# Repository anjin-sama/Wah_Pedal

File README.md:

Inductorless Wah guitar pedal effect

https://gearip.net/inductorless-wah-guitar-pedal-effect/

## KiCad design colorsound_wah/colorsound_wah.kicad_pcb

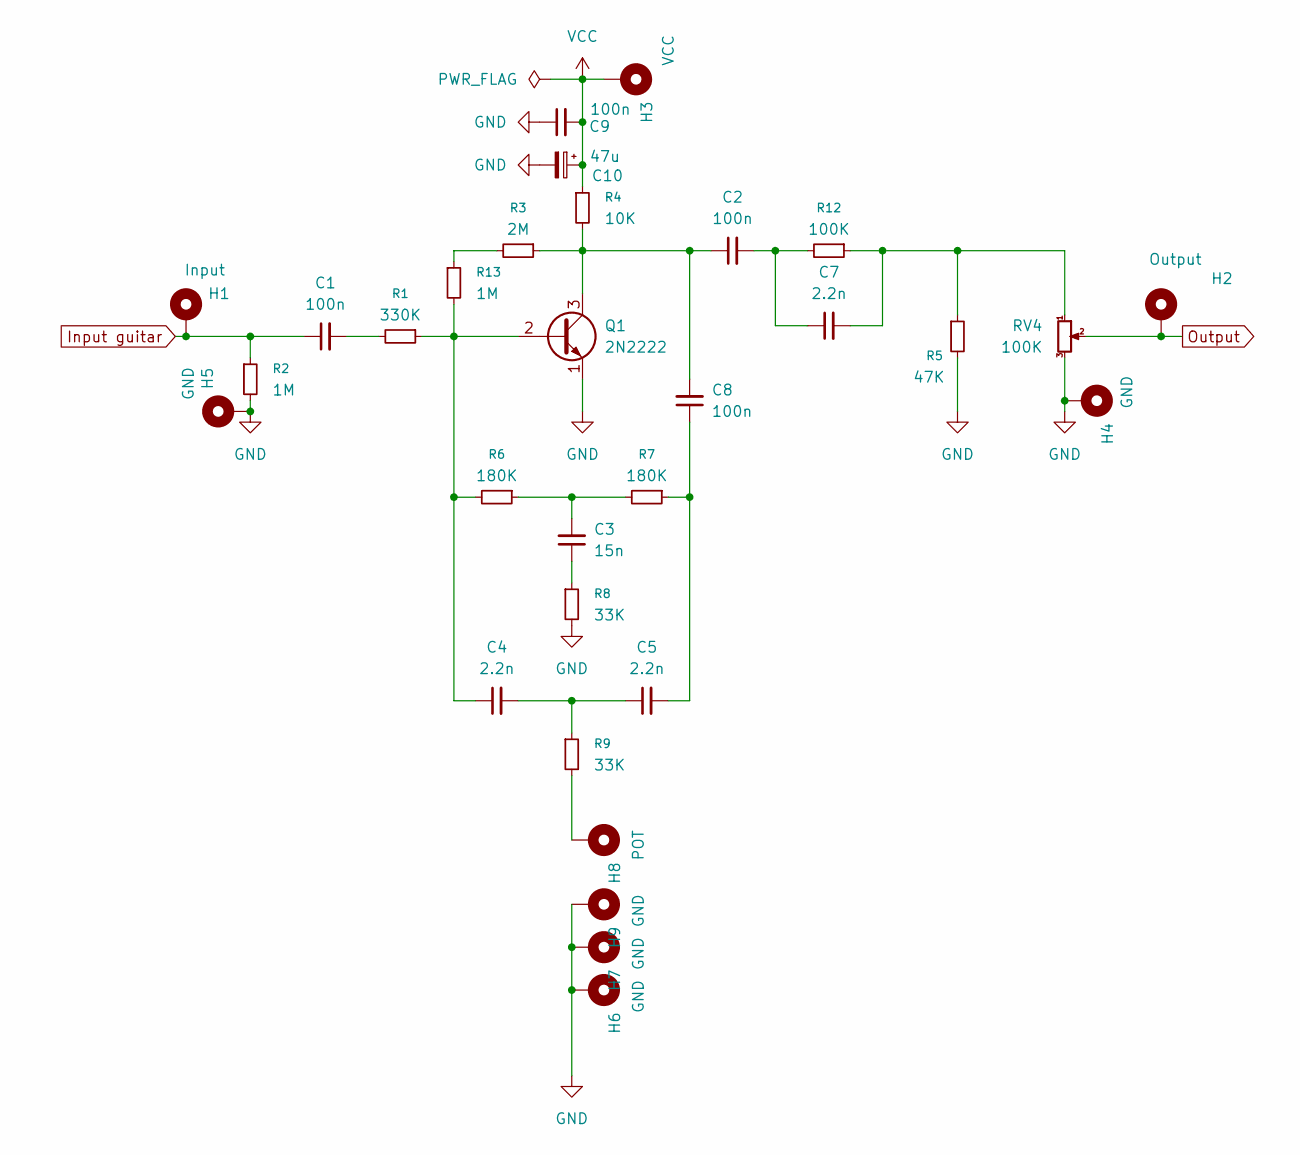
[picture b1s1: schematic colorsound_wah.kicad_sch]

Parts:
C1, C2, C8: 100n; C_Rect_L7.0mm_W2.0mm_P5.00mm
C3: 15n; C_Rect_L7.0mm_W2.0mm_P5.00mm
C4, C5, C7: 2.2n; C_Rect_L7.0mm_W2.0mm_P5.00mm
C9: 100n; C_Disc_D11.0mm_W5.0mm_P5.00mm
C10: 47u; CP_Radial_D5.0mm_P2.00mm
H1: Input; TestPoint_Loop_D2.50mm_Drill1.0mm_LowProfile
H2: Output; TestPoint_Loop_D2.50mm_Drill1.0mm_LowProfile
H3: VCC; TestPoint_Loop_D2.50mm_Drill1.0mm_LowProfile
H4, H5, H6, H7, H9: GND; TestPoint_Loop_D2.50mm_Drill1.85mm
H8: POT; TestPoint_Loop_D2.50mm_Drill1.0mm_LowProfile
Q1: 2N2222; TO-92L_Inline_Wide
R1: 330K; R_Axial_DIN0207_L6.3mm_D2.5mm_P10.16mm_Horizontal
R2, R13: 1M; R_Axial_DIN0207_L6.3mm_D2.5mm_P10.16mm_Horizontal
R3: 2M; R_Axial_DIN0207_L6.3mm_D2.5mm_P10.16mm_Horizontal
R4: 10K; R_Axial_DIN0207_L6.3mm_D2.5mm_P10.16mm_Horizontal
R5: 47K; R_Axial_DIN0207_L6.3mm_D2.5mm_P10.16mm_Horizontal
R6, R7: 180K; R_Axial_DIN0207_L6.3mm_D2.5mm_P10.16mm_Horizontal
R8, R9: 33K; R_Axial_DIN0207_L6.3mm_D2.5mm_P10.16mm_Horizontal
R12: 100K; R_Axial_DIN0207_L6.3mm_D2.5mm_P10.16mm_Horizontal
RV4: 100K; Potentiometer_ACP_CA9-H5_Horizontal

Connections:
GND: C9.1, C10.2, H4.1, H5.1, H6.1, H7.1, H9.1, Q1.1 (E), R2.2, R5.2, R8.2, RV4.3
Input guitar: C1.1, H1.1, R2.1
unnamed: C1.2, R1.2
unnamed: C2.2, C7.1, R12.2
unnamed: C3.1, R8.1
unnamed: C3.2, R6.1, R7.2
unnamed: C4.2, C5.1, R9.1
unnamed: C5.2, C8.1, R7.1
unnamed: C7.2, R5.1, R12.1, RV4.1
unnamed: H8.1, R9.2
unnamed: C4.1, Q1.2 (B), R1.1, R6.2, R13.2
unnamed: C2.1, C8.2, Q1.3 (C), R3.1, R4.2
unnamed: R3.2, R13.1
Output: H2.1, RV4.2
VCC: C9.2, C10.1, H3.1, R4.1

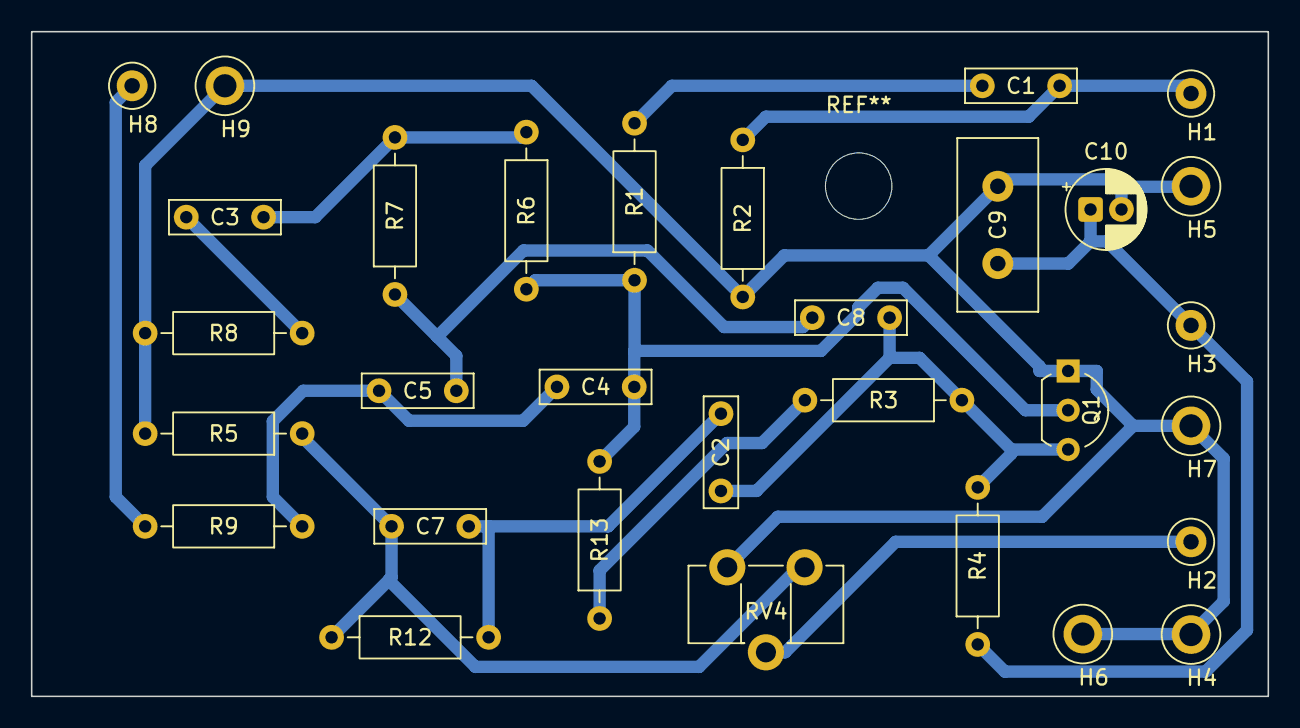
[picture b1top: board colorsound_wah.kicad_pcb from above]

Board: 2 copper layers, 80.0 x 43.0 mm, 31 parts (0 on the bottom side), 15 nets.

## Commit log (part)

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2025-12-07 upodate
